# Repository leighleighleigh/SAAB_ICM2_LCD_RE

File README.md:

# SAAB_ICM2_LCD_RE
Collection of schematics and resources I've collected while reverse-engineering the LCD used in SAAB 9-3 "Infotainment Control Module 2".

## Directory Descriptions
- Arduino_ESP8266_ICM2_Development
    - This is the PIO environment where I developed the Arduino_SAAB_ICM2_LCD_Driver, for this display.
    - This driver is referenced as a git submodule.
- BusPirate_ReverseEngineering_PythonScripts
    - While I was first reverse-engineering the I2C commands for the display, I wrote a couple terrible-named scripts to drive the BusPirate v3 I was using.
    - I then chose to move to a C-library, as the BusPirate is incredibly slow!
    - But we have to start somewhere, so I'm keeping this here to "show the process".
- ICM2_PCB_PICS
    - Here you will find actual pictures of the ICM2 PCB, and some have been creatively overlaid in photoshop to allow me to visually trace the connections.
    - This helped me develop a wiring schematic for the display...
- KICAD_SAAB_ICM2_Display
    - Here is the aforementioned schematic, a PDF printout has been supplied for convenience.
    - There are also alot of other notes there pertaining to interfacing with the module.
- KINGSTVIS_DLA_LOGS
    - Here are some KingstVIS digital logic analyser files, which I initially used to sniff the I2C lines (before I even KNEW they were I2C lines.).
    - I then used this info to take it over to the BusPirate and begin reverse-engineering.
- TEST_GRAPHICS
    - Some bitmaps/PSD files I used/made to test the display. 
    - There is a SAAB one, which I thought looked cool.
    - There is also one called "Froggy Chair", which is a reference to the video game series "Animal Crossing".

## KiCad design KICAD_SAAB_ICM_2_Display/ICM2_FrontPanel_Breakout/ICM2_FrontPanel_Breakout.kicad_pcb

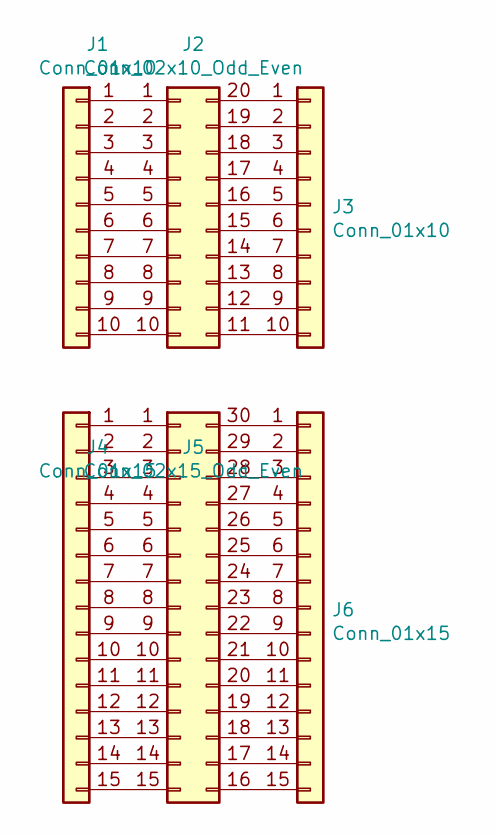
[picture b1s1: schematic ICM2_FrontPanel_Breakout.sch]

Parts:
J1, J3: Conn_01x10; PinSocket_1x10_P2.54mm_Vertical_SMD_Pin1Left
J2: Conn_02x10_Odd_Even; Hirose_FH12-20S-0.5SH_1x20-1MP_P0.50mm_Horizontal
J4, J6: Conn_01x15; PinSocket_1x15_P2.54mm_Vertical_SMD_Pin1Left
J5: Conn_02x15_Odd_Even; Hirose_FH12-30S-0.5SH_1x30-1MP_P0.50mm_Horizontal

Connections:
unnamed: J1.1, J2.1
unnamed: J1.2, J2.2
unnamed: J1.3, J2.3
unnamed: J1.4, J2.4
unnamed: J1.5, J2.5
unnamed: J1.6, J2.6
unnamed: J1.7, J2.7
unnamed: J1.8, J2.8
unnamed: J1.9, J2.9
unnamed: J1.10, J2.10
unnamed: J2.11, J3.10
unnamed: J2.12, J3.9
unnamed: J2.13, J3.8
unnamed: J2.14, J3.7
unnamed: J2.15, J3.6
unnamed: J2.16, J3.5
unnamed: J2.17, J3.4
unnamed: J2.18, J3.3
unnamed: J2.19, J3.2
unnamed: J2.20, J3.1
unnamed: J4.1, J5.1
unnamed: J4.2, J5.2
unnamed: J4.3, J5.3
unnamed: J4.4, J5.4
unnamed: J4.5, J5.5
unnamed: J4.6, J5.6
unnamed: J4.7, J5.7
unnamed: J4.8, J5.8
unnamed: J4.9, J5.9
unnamed: J4.10, J5.10
unnamed: J4.11, J5.11
unnamed: J4.12, J5.12
unnamed: J4.13, J5.13
unnamed: J4.14, J5.14
unnamed: J4.15, J5.15
unnamed: J5.16, J6.15
unnamed: J5.17, J6.14
unnamed: J5.18, J6.13
unnamed: J5.19, J6.12
unnamed: J5.20, J6.11
unnamed: J5.21, J6.10
unnamed: J5.22, J6.9
unnamed: J5.23, J6.8
unnamed: J5.24, J6.7
unnamed: J5.25, J6.6
unnamed: J5.26, J6.5
unnamed: J5.27, J6.4
unnamed: J5.28, J6.3
unnamed: J5.29, J6.2
unnamed: J5.30, J6.1

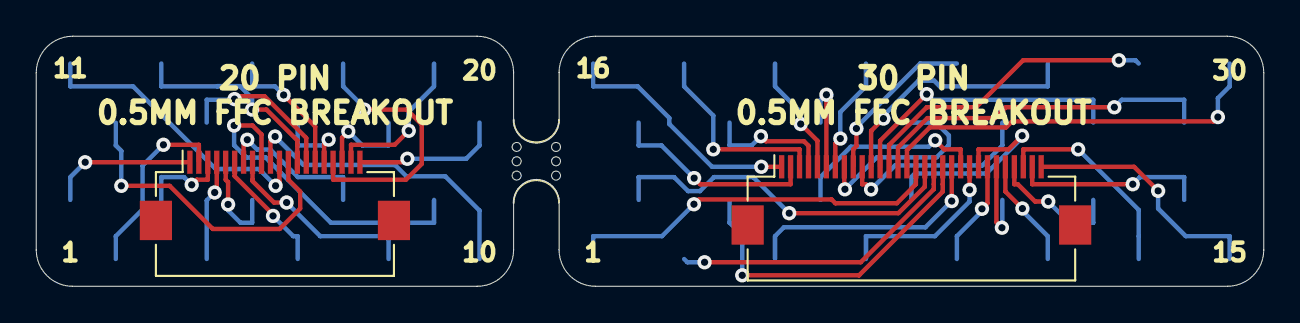
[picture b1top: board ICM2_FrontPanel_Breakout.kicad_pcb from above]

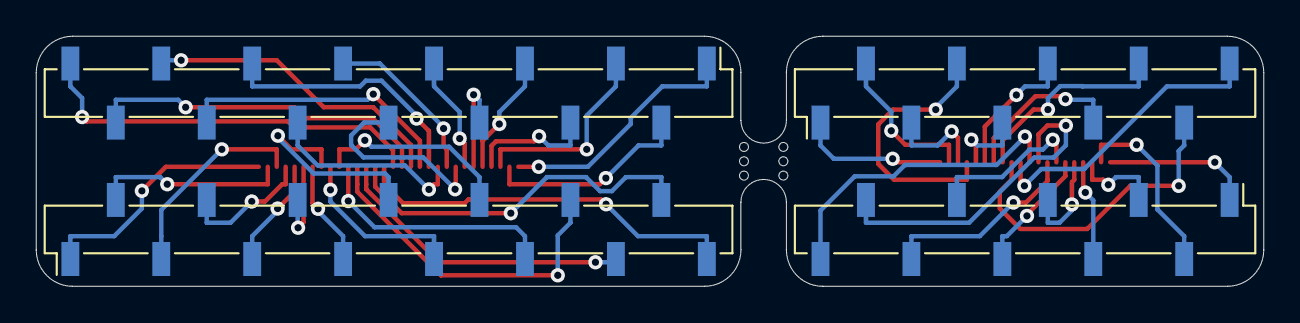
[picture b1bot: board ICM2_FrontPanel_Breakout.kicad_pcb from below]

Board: 2 copper layers, 68.6 x 14.0 mm, 7 parts (4 on the bottom side), 50 nets.

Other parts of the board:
mouse-bite-2.54mm-slot: VAL**; mouse-bite-2.54mm-slot

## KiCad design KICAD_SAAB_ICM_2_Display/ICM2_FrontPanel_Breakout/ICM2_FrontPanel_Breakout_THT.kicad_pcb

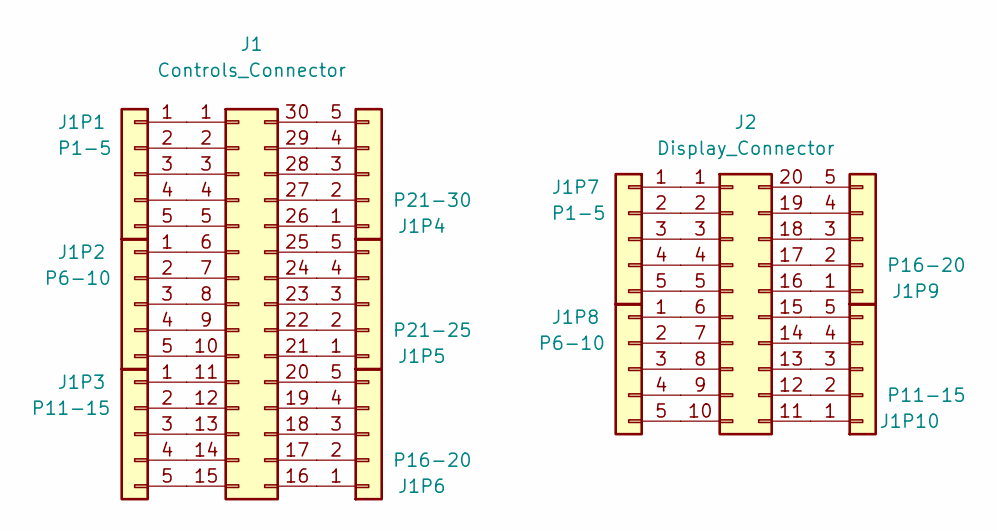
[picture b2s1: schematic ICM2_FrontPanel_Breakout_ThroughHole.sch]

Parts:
J1: Controls_Connector; Hirose_FH12-30S-0.5SH_1x30-1MP_P0.50mm_Horizontal
J1P1, J1P7: P1-5; PinHeader_1x05_P2.54mm_Vertical_Simple
J1P2, J1P8: P6-10; PinHeader_1x05_P2.54mm_Vertical_Simple
J1P3, J1P10: P11-15; PinHeader_1x05_P2.54mm_Vertical_Simple
J1P4: P21-30; PinHeader_1x05_P2.54mm_Vertical_Simple
J1P5: P21-25; PinHeader_1x05_P2.54mm_Vertical_Simple
J1P6, J1P9: P16-20; PinHeader_1x05_P2.54mm_Vertical_Simple
J2: Display_Connector; Hirose_FH12-20S-0.5SH_1x20-1MP_P0.50mm_Horizontal

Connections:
unnamed: J1.1, J1P1.1
unnamed: J1.2, J1P1.2
unnamed: J1.3, J1P1.3
unnamed: J1.4, J1P1.4
unnamed: J1.5, J1P1.5
unnamed: J1.6, J1P2.1
unnamed: J1.7, J1P2.2
unnamed: J1.8, J1P2.3
unnamed: J1.9, J1P2.4
unnamed: J1.10, J1P2.5
unnamed: J1.11, J1P3.1
unnamed: J1.12, J1P3.2
unnamed: J1.13, J1P3.3
unnamed: J1.14, J1P3.4
unnamed: J1.15, J1P3.5
unnamed: J1.16, J1P6.1
unnamed: J1.17, J1P6.2
unnamed: J1.18, J1P6.3
unnamed: J1.19, J1P6.4
unnamed: J1.20, J1P6.5
unnamed: J1.21, J1P5.1
unnamed: J1.22, J1P5.2
unnamed: J1.23, J1P5.3
unnamed: J1.24, J1P5.4
unnamed: J1.25, J1P5.5
unnamed: J1.26, J1P4.1
unnamed: J1.27, J1P4.2
unnamed: J1.28, J1P4.3
unnamed: J1.29, J1P4.4
unnamed: J1.30, J1P4.5
unnamed: J1P7.1, J2.1
unnamed: J1P7.2, J2.2
unnamed: J1P7.3, J2.3
unnamed: J1P7.4, J2.4
unnamed: J1P7.5, J2.5
unnamed: J1P8.1, J2.6
unnamed: J1P8.2, J2.7
unnamed: J1P8.3, J2.8
unnamed: J1P8.4, J2.9
unnamed: J1P8.5, J2.10
unnamed: J1P9.1, J2.16
unnamed: J1P9.2, J2.17
unnamed: J1P9.3, J2.18
unnamed: J1P9.4, J2.19
unnamed: J1P9.5, J2.20
unnamed: J1P10.1, J2.11
unnamed: J1P10.2, J2.12
unnamed: J1P10.3, J2.13
unnamed: J1P10.4, J2.14
unnamed: J1P10.5, J2.15

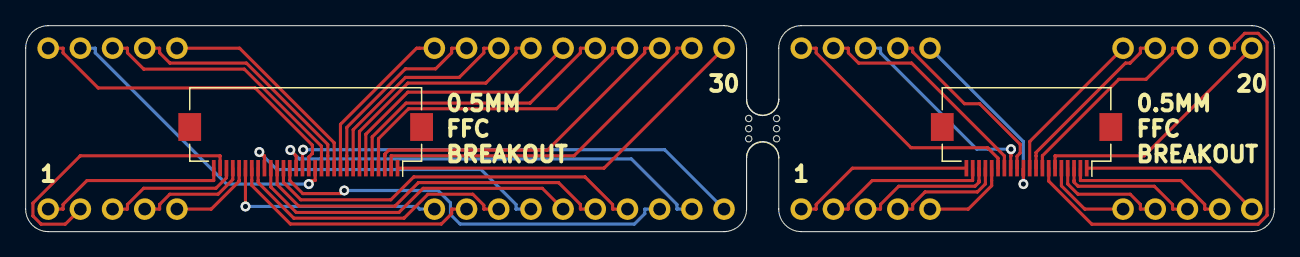
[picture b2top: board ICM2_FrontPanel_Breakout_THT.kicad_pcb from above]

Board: 2 copper layers, 98.6 x 16.3 mm, 13 parts (0 on the bottom side), 50 nets.

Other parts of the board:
mouse-bite-2.54mm-slot: VAL**; mouse-bite-2.54mm-slot

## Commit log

2020-04-06 Initial transfer to git
2020-04-06 Fixing submodule
2020-04-06 Hopefully fixed submodule reference for LCD driver
2020-04-06 Fixed typo in library name, sorry Adafruit!
2020-04-06 Updated schematic PDF and README
2020-04-21 Added the photos uploaded to Hackaday project, for archival purposes.
2020-04-25 Playing with a simple music interface, nothing good yet.
2020-04-28 Playing with text effects, imported Adafruit_GFX directly
2020-05-06 Playing with the display library, added some more pics up on Hackaday
2020-05-12 Working on simple FPC breakouts, as commercial ones are hard to find.
2020-05-21 Further refined FFC breakout board, quite happy with this design.
2020-08-19 Experimenting with alternate style breakout for FFC cables
